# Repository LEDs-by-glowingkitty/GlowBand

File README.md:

GlowBand is an exciting LED wristband. For dancing at parties and festivals, for long-time exposure photography, and for everyday situations that need some light.

This project started as "The Glowing Arms Project" (check out the "GlowBand v0.1" folder) and after experimenting with making the project smaller and based on existing PCBs ("GlowBand v0.2" folder) I decided to instead make a custom PCB design ("GlowBand v1.0"). The PCB design is still in development, but I plan to finish the design in the coming months. Stay tuned!

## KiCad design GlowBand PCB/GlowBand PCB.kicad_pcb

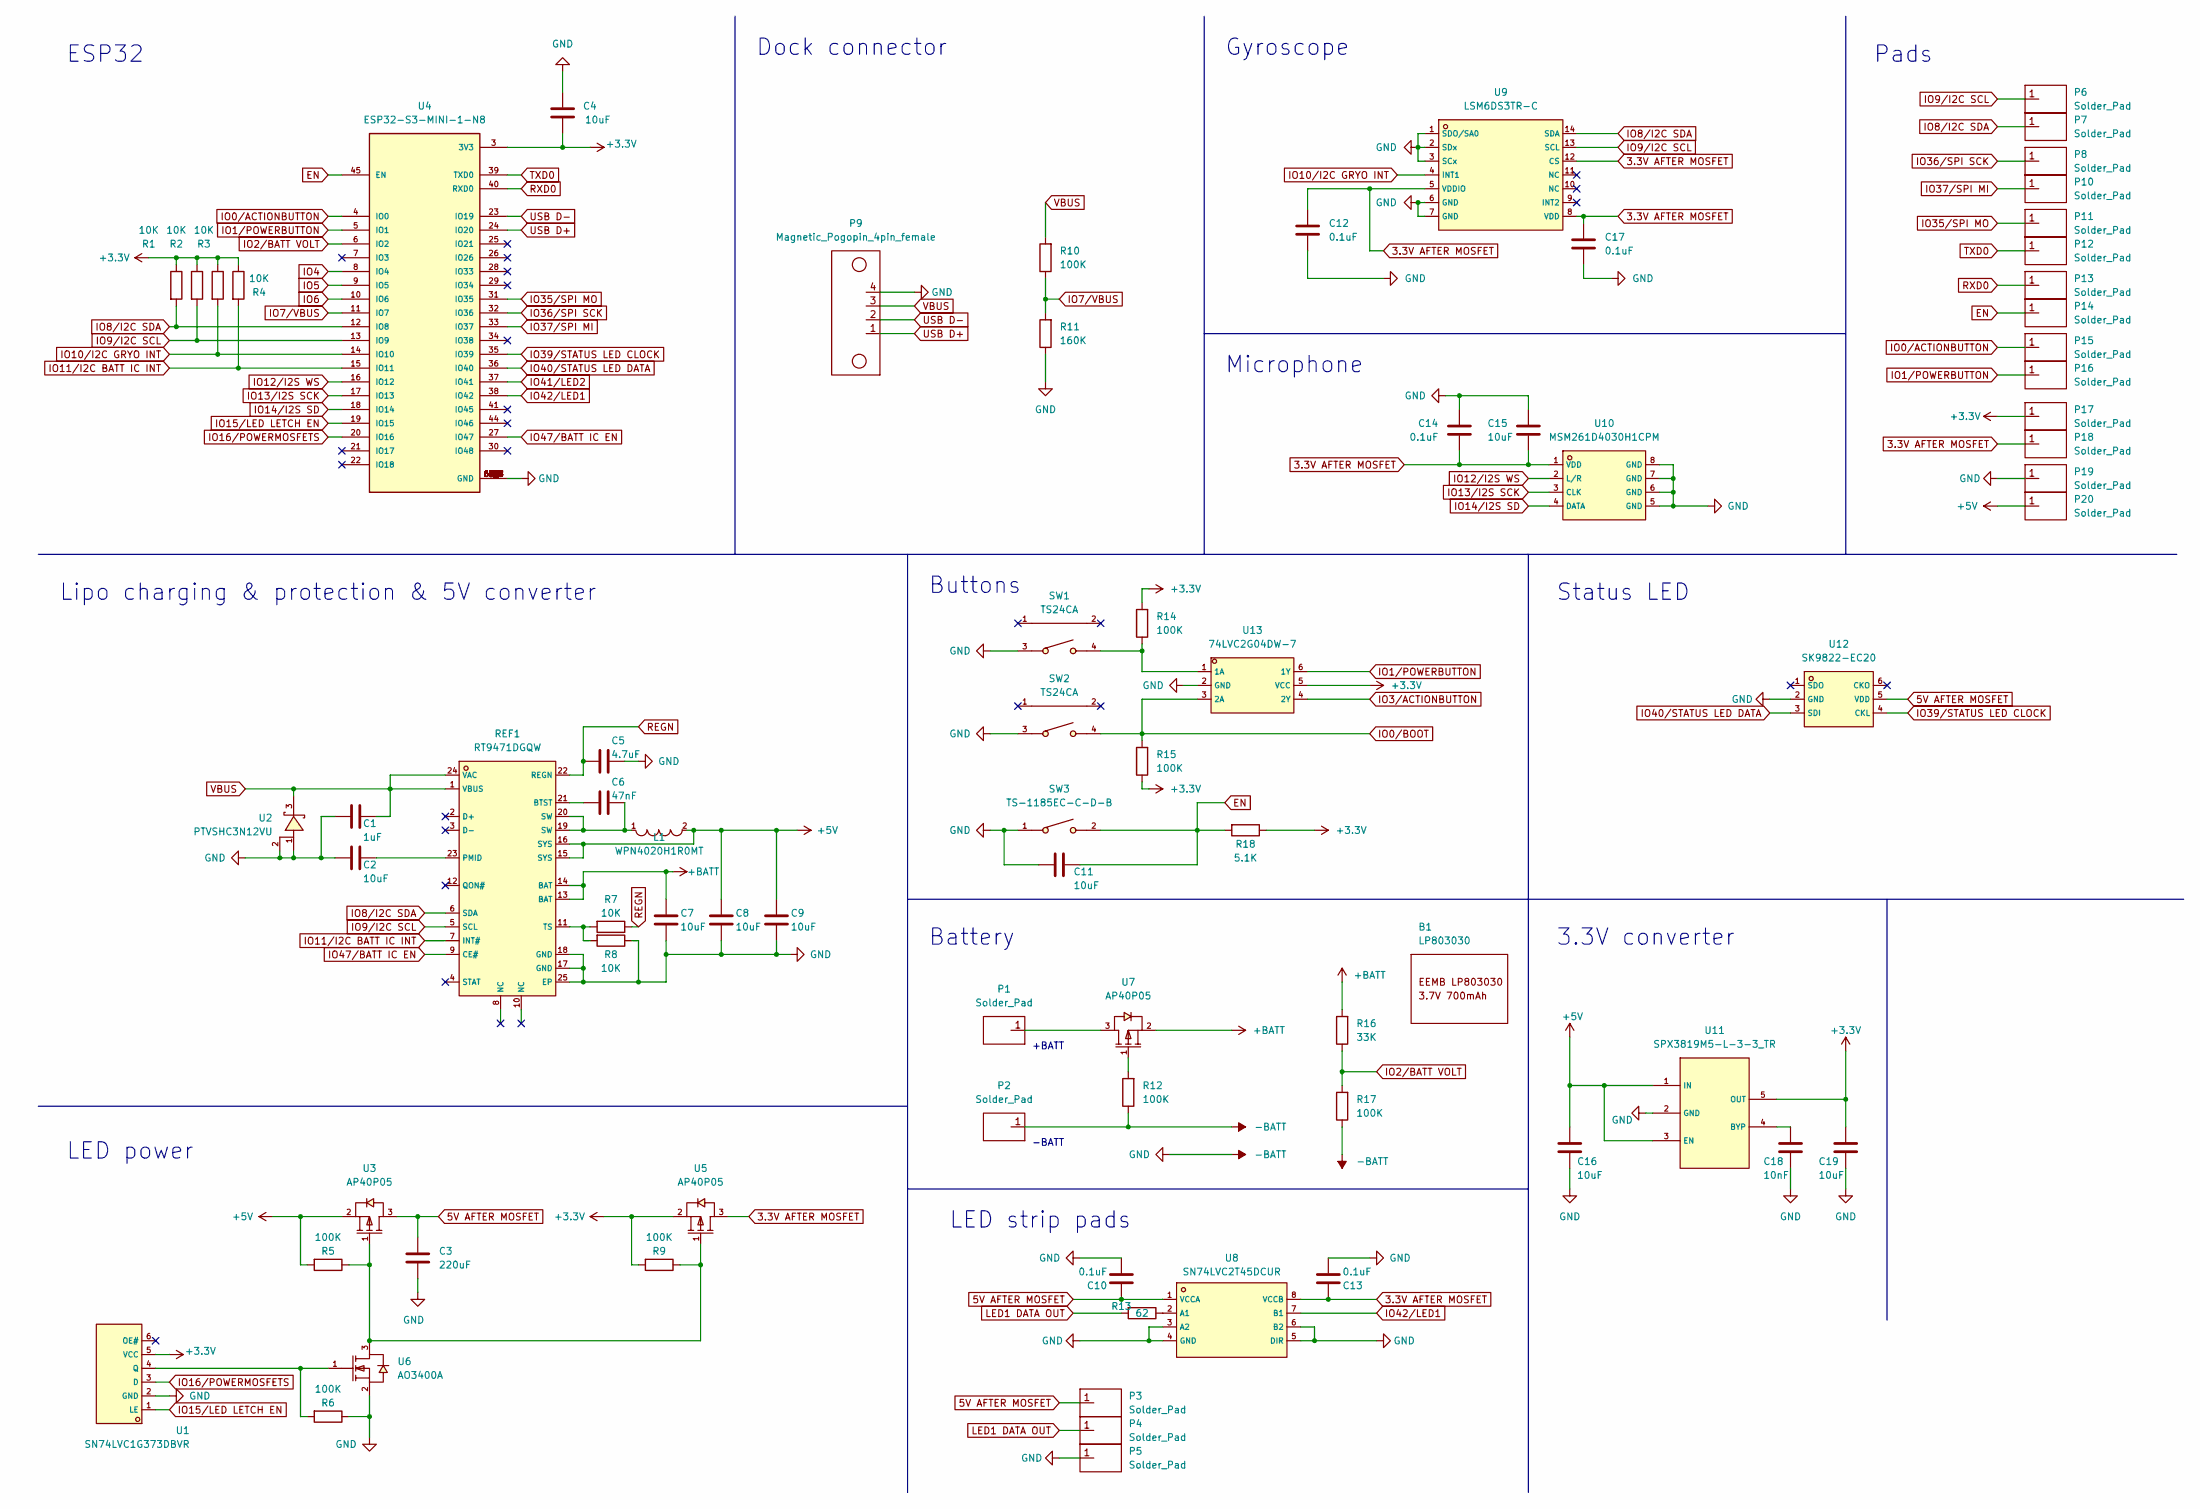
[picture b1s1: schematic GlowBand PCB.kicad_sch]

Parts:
B1: LP803030
C1: 1uF; C_0402_1005Metric; LCSC # C52923
C2, C4, C7, C8, C9, C15, C16, C19: 10uF; C_0603_1608Metric; LCSC # C96446
C3: 220uF; C_1206_3216Metric; LCSC # C412252
C5: 4.7uF; C_0402_1005Metric; LCSC # C23733
C6: 47nF; C_0402_1005Metric; LCSC # C505502
C10, C12, C13, C14, C17: 0.1uF; C_0402_1005Metric; LCSC # C1525
C11: 10uF; C_0603_1608Metric; LCSC # C19702
C18: 10nF; C_0402_1005Metric; LCSC # C15195
L1: WPN4020H1R0MT; IND-SMD_L4.0-W4.0_SLW40XX; LCSC C98359
P1, P2, P3, P4, P5, P6, P7, P8, P10, P11, P12, P13, P14, P15, P16, P17, P18, P19, P20: Solder_Pad; Solder pad
P9: Magnetic_Pogopin_4pin_female; Magnetic Pogopin 4pin female
R1, R2, R3, R4, R7, R8: 10K; R_0402_1005Metric; LCSC # C25744
R5, R6, R9, R10, R12, R14, R15, R17: 100K; R_0402_1005Metric; LCSC # C25741
R11: 160K; R_0603_1608Metric; LCSC # C22813
R13: 62; R_0402_1005Metric; LCSC # C4962
R16: 33K; R_0402_1005Metric; LCSC # C25779
R18: 5.1K; R_0402_1005Metric; LCSC # C25905
REF1: RT9471DGQW; RT9471_vias_in_pad; LCSC C2839437
SW1, SW2: TS24CA; SW-SMD_TS24CA; LCSC C393942
SW3: TS-1185EC-C-D-B; SW-SMD_4P-L3.7-W3.0-P1.50-LS4.7; LCSC # C318893
U1: SN74LVC1G373DBVR; SOT-23-6_L2.9-W1.6-P0.95-LS2.8-BR; LCSC C128413
U2: PTVSHC3N12VU; DFN-3_L2.0-W2.0-P1.30-BR; LCSC C110755
U3, U5, U7: AP40P05; SOT-23-3_L2.9-W1.3-P1.90-LS2.4-BR; LCSC # C2886385
U4: ESP32-S3-MINI-1-N8; LCSC# C2913206
U6: AO3400A; SOT-23-3_L2.9-W1.6-P1.90-LS2.8-BR; LCSC # C20917
U8: SN74LVC2T45DCUR; VSSOP-8_L2.4-W2.1-P0.50-LS3.2-BR; LCSC # C15741
U9: LSM6DS3TR-C; LGA-14_L3.0-W2.5-P0.50-TL; LCSC C967633
U10: MSM261D4030H1CPM; MIC-SMD_8P-L3.0-W4.0-P0.85-BL; LCSC # C966942
U11: SPX3819M5-L-3-3_TR; SOT-23-5_L3.0-W1.7-P0.95-LS2.8-BR; LCSC # C9055
U12: SK9822-EC20; LED-SMD_6P-L2.0-W2.0-P0.80-TL; LCSC C2909059
U13: 74LVC2G04DW-7; SOT-363_L2.0-W1.3-P0.65-LS2.1-BR; LCSC C69053

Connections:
3.3V AFTER MOSFET: C12.1, C13.1, C14.2, C15.2, C17.1, P18.1, U5.3 (D), U8.8 (VCCB), U9.5 (VDDIO), U9.8 (VDD), U9.12 (CS), U10.1 (VDD)
5V AFTER MOSFET: C3.1, C10.1, P3.1, U3.3 (D), U8.1 (VCCA), U12.5 (VDD)
+3V3: C4.2, C19.2, P17.1, R1.1, R2.1, R3.1, R4.1, R9.2, R14.2, R15.1, R18.1, U1.5 (VCC), U4.3 (3V3), U5.2 (S), U11.5 (OUT), U13.5 (VCC)
+5V: C8.2, C9.2, C16.2, L1.2, P20.1, R5.2, REF1.15 (SYS), REF1.16 (SYS), U3.2 (S), U11.1 (IN), U11.3 (EN)
+BATT: C7.2, R16.2, REF1.13 (BAT), REF1.14 (BAT), U7.2 (S)
-BATT: C1.1, C2.1, C3.2, C4.1, C5.2, C7.1, C8.1, C9.1, C10.2, C11.1, C12.2, C13.2, C14.1, C15.1, C16.1, C17.2, C18.1, C19.1, P2.1, P5.1, P9.4, P19.1, R6.1, R8.1, R11.1, R12.1, R17.1, REF1.17 (GND), REF1.18 (GND), REF1.25 (EP), SW1.3, SW2.3, SW3.1, U1.2 (GND), U2.1 (A), U2.2 (1), U4.1 (GND), U4.2 (GND), U4.42 (GND), U4.43 (GND), U4.46 (GND), U4.47 (GND), U4.48 (GND), U4.49 (GND), U4.50 (GND), U4.51 (GND), U4.52 (GND), U4.53 (GND), U4.54 (GND), U4.55 (GND), U4.56 (GND), U4.57 (GND), U4.58 (GND), U4.59 (GND), U4.60 (GND), U4.61 (GND), U4.61_1 (GND), U4.61_2 (GND), U4.61_3 (GND), U4.61_4 (GND), U4.61_5 (GND), U4.61_6 (GND), U4.61_7 (GND), U4.61_8 (GND), U4.62 (GND), U4.63 (GND), U4.64 (GND), U4.65 (GND), U6.2 (S), U8.3 (A2), U8.4 (GND), U8.5 (DIR), U8.6 (B2), U9.1 (SDO/SA0), U9.2 (SDx), U9.3 (SCx), U9.6 (GND), U9.7 (GND), U10.5 (GND), U10.6 (GND), U10.7 (GND), U10.8 (GND), U11.2 (GND), U12.2 (GND), U13.2 (GND)
EN: C11.2, P14.1, R18.2, SW3.2, U4.45 (EN)
IO0/ACTIONBUTTON: P15.1, U4.4 (IO0)
IO0/BOOT: R15.2, SW2.4, U13.3 (2A)
IO1/POWERBUTTON: P16.1, U4.5 (IO1), U13.6 (1Y)
IO2/BATT VOLT: R16.1, R17.2, U4.6 (IO2)
IO3/ACTIONBUTTON: U13.4 (2Y)
IO4: U4.8 (IO4)
IO5: U4.9 (IO5)
IO6: U4.10 (IO6)
IO7/VBUS: R10.1, R11.2, U4.11 (IO7)
IO8/I2C SDA: P7.1, R1.2, REF1.6 (SDA), U4.12 (IO8), U9.14 (SDA)
IO9/I2C SCL: P6.1, R2.2, REF1.5 (SCL), U4.13 (IO9), U9.13 (SCL)
IO10/I2C GRYO INT: R3.2, U4.14 (IO10), U9.4 (INT1)
IO11/I2C BATT IC INT: R4.2, REF1.7 (INT#), U4.15 (IO11)
IO12/I2S WS: U4.16 (IO12), U10.2 (L/R)
IO13/I2S SCK: U4.17 (IO13), U10.3 (CLK)
IO14/I2S SD: U4.18 (IO14), U10.4 (DATA)
IO15/LED LETCH EN: U1.1 (LE), U4.19 (IO15)
IO16/POWERMOSFETS: U1.3 (D), U4.20 (IO16)
IO35/SPI MO: P11.1, U4.31 (IO35)
IO36/SPI SCK: P8.1, U4.32 (IO36)
IO37/SPI MI: P10.1, U4.33 (IO37)
IO39/STATUS LED CLOCK: U4.35 (IO39), U12.4 (CKL)
IO40/STATUS LED DATA: U4.36 (IO40), U12.3 (SDI)
IO41/LED2: U4.37 (IO41)
IO42/LED1: U4.38 (IO42), U8.7 (B1)
IO47/BATT IC EN: REF1.9 (CE#), U4.27 (IO47)
LED1 DATA OUT: P4.1, R13.2
unnamed: C2.2, REF1.23 (PMID)
unnamed: C6.1, REF1.21 (BTST)
unnamed: C6.2, L1.1, REF1.19 (SW), REF1.20 (SW)
unnamed: C18.2, U11.4 (BYP)
unnamed: P1.1, U7.3 (D)
unnamed: R5.1, R9.1, U3.1 (G), U5.1 (G), U6.3 (D)
unnamed: R6.2, U1.4 (Q), U6.1 (G)
unnamed: R7.2, R8.2, REF1.11 (TS)
unnamed: R12.2, U7.1 (G)
unnamed: R13.1, U8.2 (A1)
unnamed: R14.1, SW1.4, U13.1 (1A)
REGN: C5.1, R7.1, REF1.22 (REGN)
RXD0: P13.1, U4.40 (RXD0)
TXD0: P12.1, U4.39 (TXD0)
USB D+: P9.1, U4.24 (IO20)
USB D-: P9.2, U4.23 (IO19)
VBUS: C1.2, P9.3, R10.2, REF1.1 (VBUS), REF1.24 (VAC), U2.3 (K)

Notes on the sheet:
+BATT
Dock connector
ESP32
LED strip pads
Buttons
LED power
3.3V converter
Status LED
Gyroscope
Microphone
-BATT
Lipo charging & protection & 5V converter
Pads
Battery

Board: 2 copper layers, 76 parts (18 on the bottom side), 46 nets, no tracks yet.

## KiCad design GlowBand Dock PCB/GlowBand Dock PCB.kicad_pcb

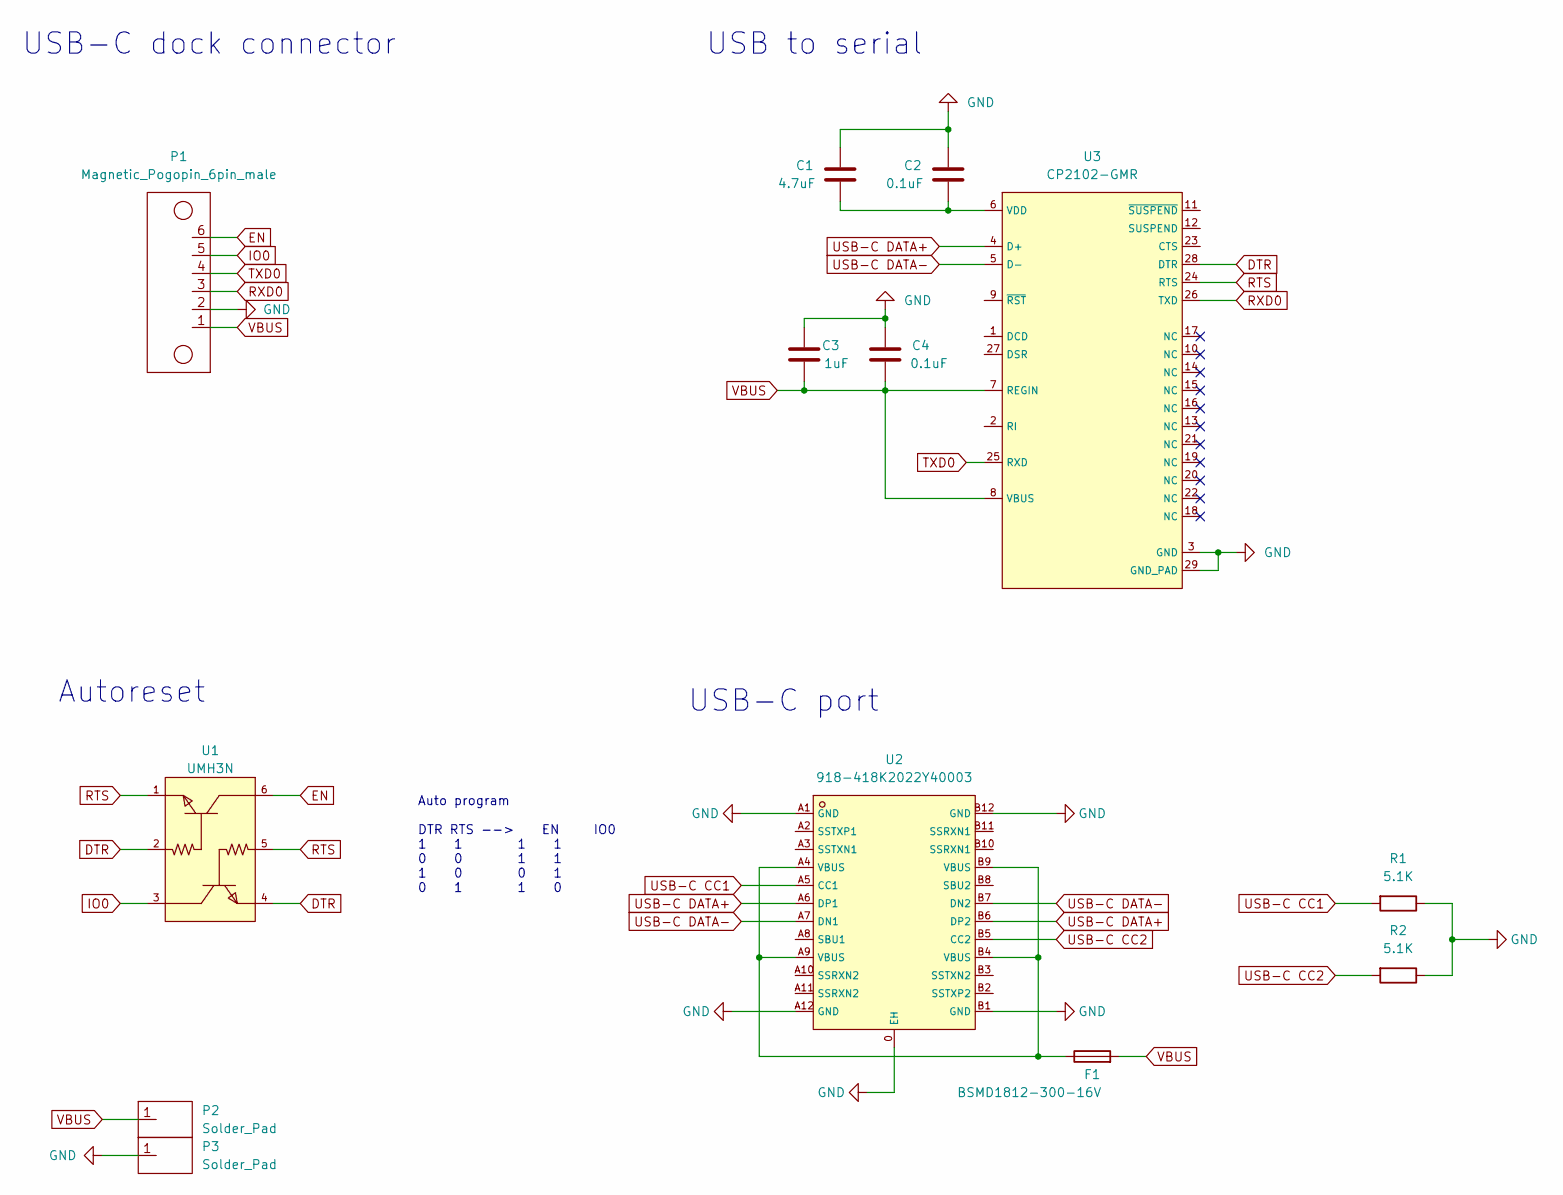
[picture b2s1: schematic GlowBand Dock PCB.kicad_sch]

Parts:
C1: 4.7uF; C_0603_1608Metric; LCSC # C19666
C2, C4: 0.1uF; C_0402_1005Metric; LCSC # C1525
C3: 1uF; C_0402_1005Metric; LCSC # C52923
F1: BSMD1812-300-16V; Fuse_1812_4532Metric; LCSC # C883162
P1: Magnetic_Pogopin_6pin_male; Magnetic Pogopin 6pin male
P2, P3: Solder_Pad; Solder pad
R1, R2: 5.1K; R_0402_1005Metric; LCSC # C25905
U1: UMH3N; SC-70-6_L2.2-W1.3-P0.65-LS2.1-BR; LCSC # C62892
U2: 918-418K2022Y40003; TYPE-C-SMD_918-418K2022Y40003; LCSC C67382
U3: CP2102-GMR; QFN-28_L5.0-W5.0-P0.50-BL-EP; LCSC # C6568

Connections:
DTR: U1.2 (B), U1.4 (E), U3.28 (DTR)
EN: P1.6, U1.6 (C)
GND: C1.2, C2.1, C3.2, C4.2, P1.2, P3.1, R1.1, R2.1, U2.0 (EH), U2.A1 (GND), U2.A12 (GND), U2.B1 (GND), U2.B12 (GND), U3.3 (GND), U3.29 (GND_PAD)
IO0: P1.5, U1.3 (C)
unnamed: C1.1, C2.2, U3.6 (VDD)
unnamed: F1.1, U2.A4 (VBUS), U2.A9 (VBUS), U2.B4 (VBUS), U2.B9 (VBUS)
RTS: U1.1 (E), U1.5 (B), U3.24 (RTS)
RXD0: P1.3, U3.26 (TXD)
TXD0: P1.4, U3.25 (RXD)
USB-C CC1: R1.2, U2.A5 (CC1)
USB-C CC2: R2.2, U2.B5 (CC2)
USB-C DATA+: U2.A6 (DP1), U2.B6 (DP2), U3.4 (D+)
USB-C DATA-: U2.A7 (DN1), U2.B7 (DN2), U3.5 (D-)
VBUS: C3.1, C4.1, F1.2, P1.1, P2.1, U3.7 (REGIN), U3.8 (VBUS)

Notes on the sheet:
Autoreset
USB-C port
USB-C dock connector
USB to serial
Auto program DTR RTS --> EN IO0 1 1 1 1 0 0 1 1 1 0 0 1 0 1 1 0

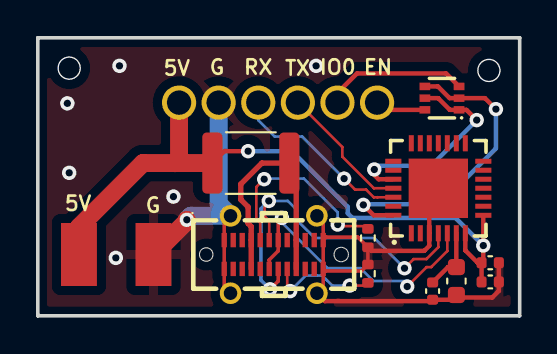
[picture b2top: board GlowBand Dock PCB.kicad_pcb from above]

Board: 2 copper layers, 26.8 x 15.4 mm, 13 parts (1 on the bottom side), 14 nets.

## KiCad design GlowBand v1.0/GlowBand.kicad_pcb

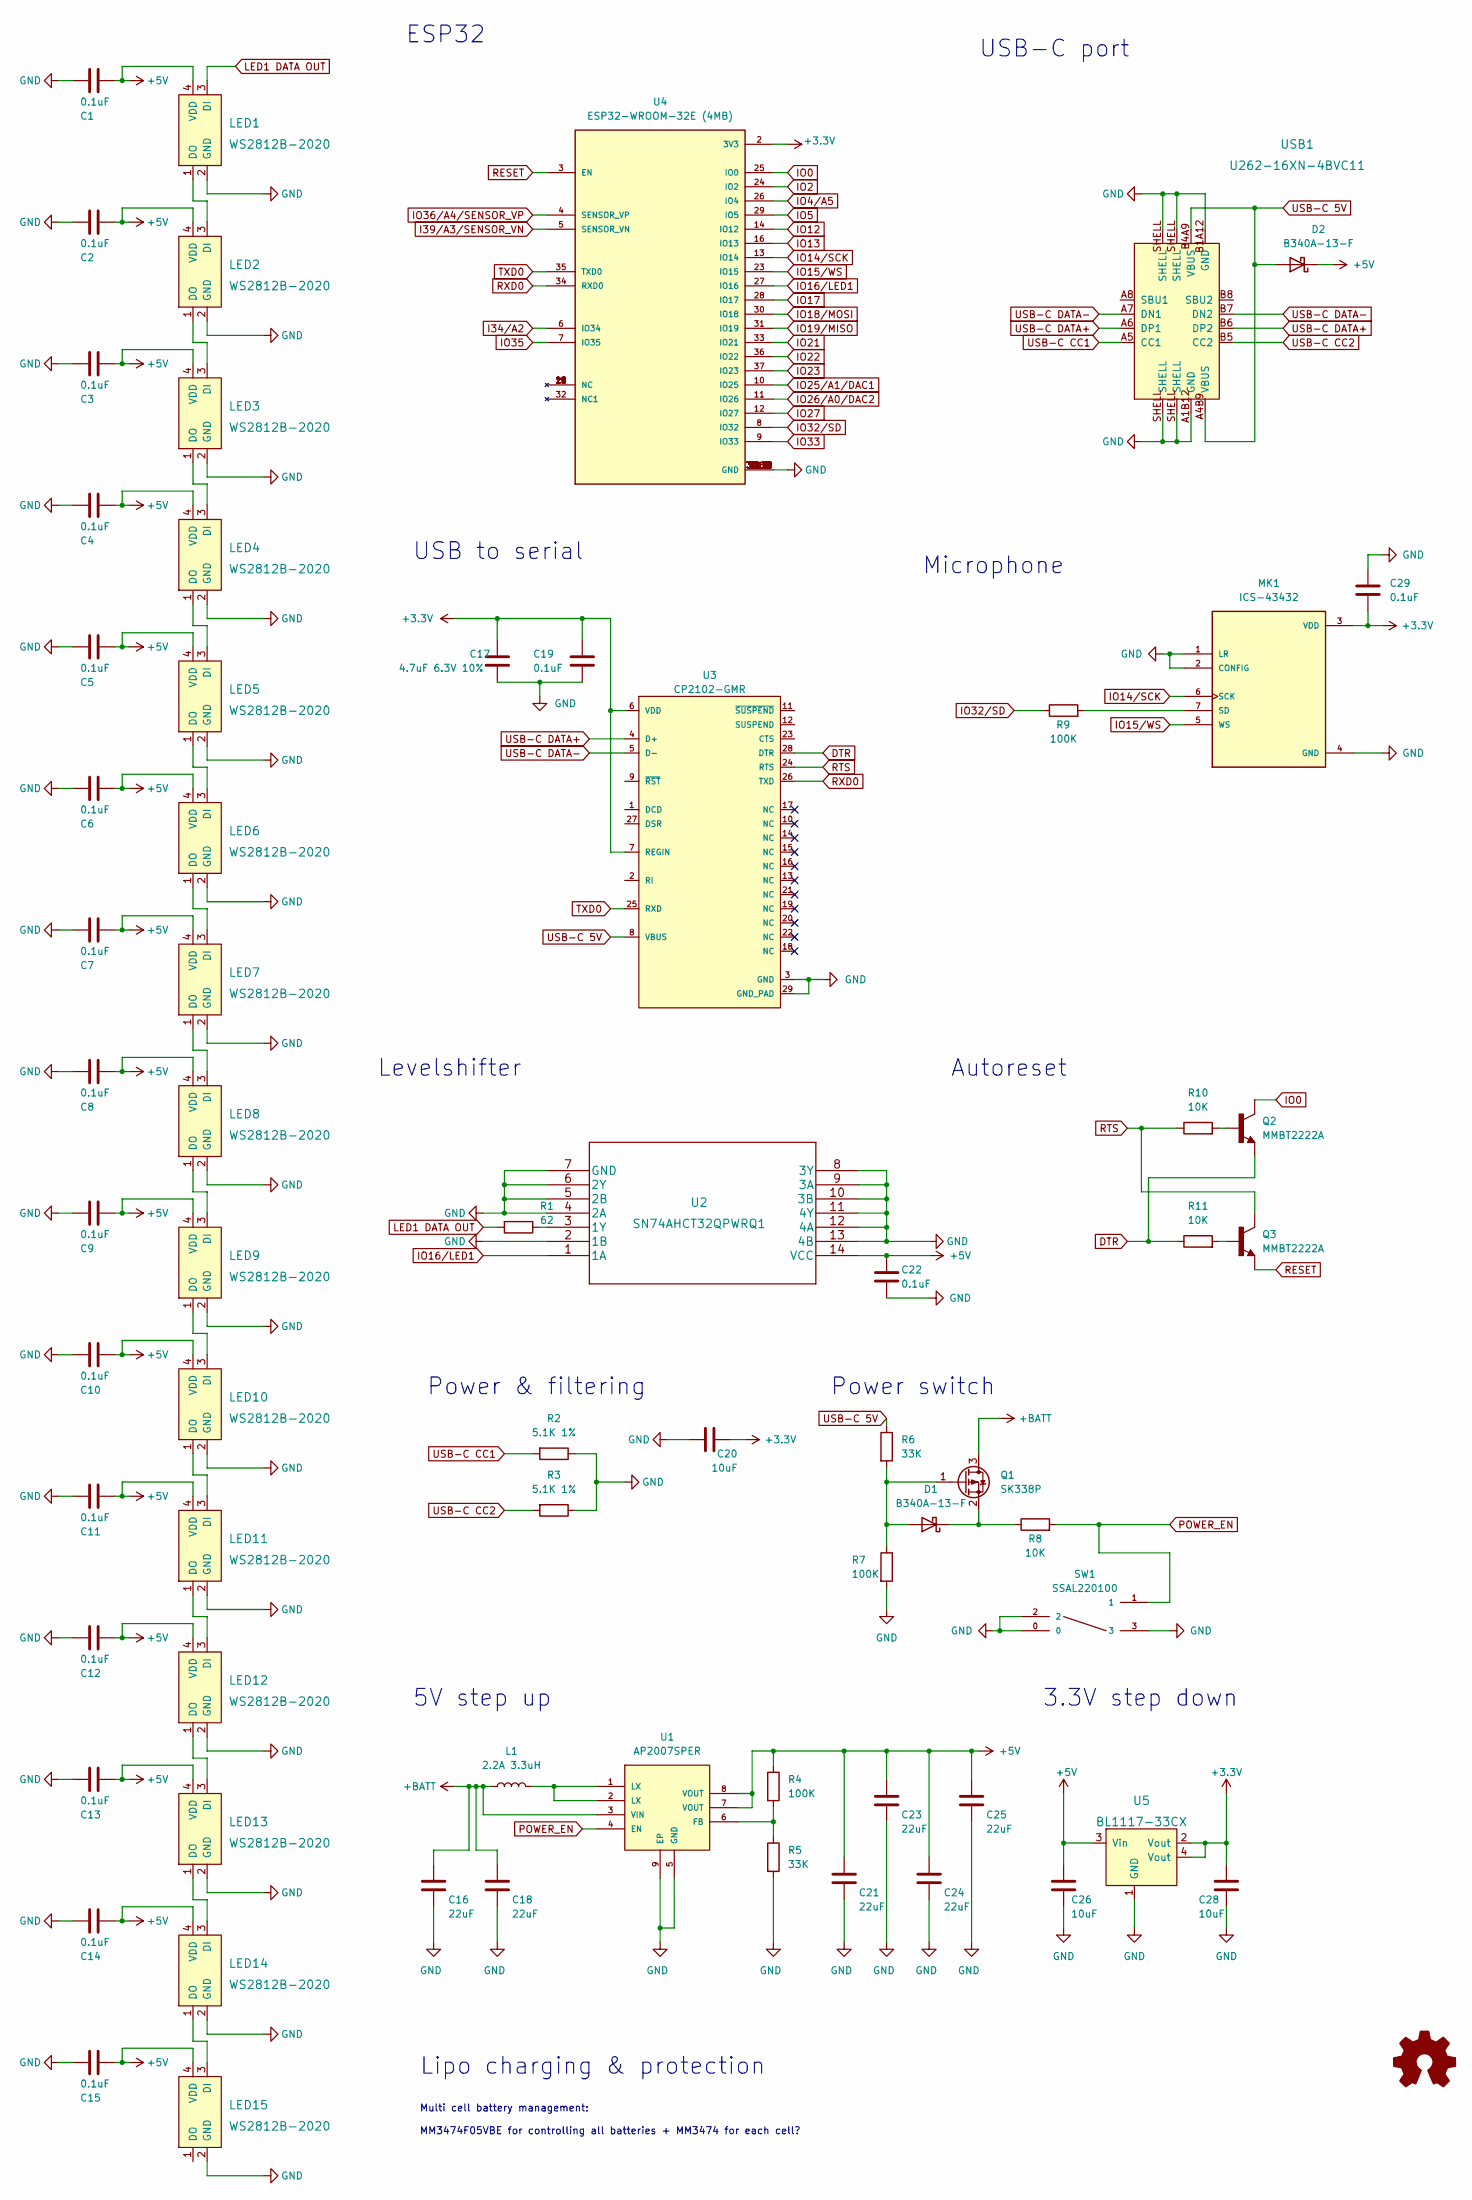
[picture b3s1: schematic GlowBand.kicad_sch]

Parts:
C1, C2, C3, C4, C5, C6, C7, C8, C9, C10, C11, C12, C13, C14, C15: 0.1uF; C_0603_1608Metric; Mfr. Part # 06035C104K4Z2A; LCSC Part # C597194
C16, C18, C21, C23, C24, C25: 22uF; C_0603_1608Metric_Pad1.08x0.95mm_HandSolder
C17: 4.7uF 6.3V 10%; C_0603_1608Metric_Pad1.08x0.95mm_HandSolder
C19, C29: 0.1uF; C_0603_1608Metric_Pad1.08x0.95mm_HandSolder; Mfr. Part # 06035C104K4Z2A; LCSC Part # C597194
C20, C26, C28: 10uF; C_0603_1608Metric_Pad1.08x0.95mm_HandSolder; Mfr. Part # C0603X5R106K250NT; LCSC Part # C729457
C22: 0.1uF; C_0603_1608Metric_Pad1.08x0.95mm_HandSolder
D1, D2: B340A-13-F; D_SMA; Mfr. Part # B340A-13-F; LCSC Part # C85098
L1: 2.2A 3.3uH; FDSD0412
LED1, LED2, LED3, LED4, LED5, LED6, LED7, LED8, LED9, LED10, LED11, LED12, LED13, LED14, LED15: WS2812B-2020; Mfr. Part # WS2812B-2020; LCSC Part # C965555
MK1: ICS-43432; MIC_ICS-43432; Mfr. Part # ICS-43432; LCSC Part # C574021
Q1: SK338P; SOT-23; Mfr. Part # SK338P; LCSC Part # C475695
Q2, Q3: MMBT2222A; SOT-23; Mfr. Part # MMBT2222A; LCSC Part # C545537
R1: 62; R_0603_1608Metric_Pad0.98x0.95mm_HandSolder
R2, R3: 5.1K 1%; R_0603_1608Metric_Pad0.98x0.95mm_HandSolder; Mfr. Part # HPCR0603F5K10K9; LCSC Part # C365193
R4, R7, R9: 100K; R_0603_1608Metric_Pad0.98x0.95mm_HandSolder; Mfr. Part # 0603WAF1003T5E; LCSC Part # C25803
R5, R6: 33K; R_0603_1608Metric_Pad0.98x0.95mm_HandSolder
R8: 10K; R_0603_1608Metric_Pad0.98x0.95mm_HandSolder
R10, R11: 10K; R_0603_1608Metric_Pad0.98x0.95mm_HandSolder; Mfr. Part # RC0603FR-0710KL; LCSC Part # C98220
SW1: SSAL220100
U1: AP2007SPER; Mfr. Part # AP2007SPER; LCSC Part # C130338
U2: SN74AHCT32QPWRQ1; Mfr. Part # SN74AHCT32QPWRQ1; LCSC Part # C507218
U3: CP2102-GMR; mouser part number 634-CP2102-GMR; digikey description USB Bridge, USB to UART USB 2.0 UART In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
U4: ESP32-WROOM-32E (4MB); MODULE_ESP32-WROOM-32E_(16MB); Mfr. Part # ESP32-WROOM-32E(4MB); LCSC Part # C701341
U5: BL1117-33CX; SOT-223; Mfr. Part # BL1117-33CX; LCSC Part # C5400
USB1: U262-16XN-4BVC11; USB-3.1-SMD_U262-161N-4BVC11; Mfr. Part # U262-161N-4BVC11; LCSC Part # C319148

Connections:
+3V3: C17.2, C19.1, C20.1, C28.2, C29.2, MK1.3 (VDD), U3.6 (VDD), U3.7 (REGIN), U4.2 (3V3), U5.2 (Vout), U5.4 (Vout)
+5V: C1.1, C2.1, C3.1, C4.1, C5.1, C6.1, C7.1, C8.1, C9.1, C10.1, C11.1, C12.1, C13.1, C14.1, C15.1, C21.1, C22.1, C23.1, C24.1, C25.1, C26.2, D2.1 (K), LED1.4 (VDD), LED2.4 (VDD), LED3.4 (VDD), LED4.4 (VDD), LED5.4 (VDD), LED6.4 (VDD), LED7.4 (VDD), LED8.4 (VDD), LED9.4 (VDD), LED10.4 (VDD), LED11.4 (VDD), LED12.4 (VDD), LED13.4 (VDD), LED14.4 (VDD), LED15.4 (VDD), R4.1, U1.7 (VOUT), U1.8 (VOUT), U2.14 (VCC), U5.3 (Vin)
+BATT: C16.1, C18.1, L1.1, Q1.3 (D), U1.3 (VIN)
DTR: Q2.2, R11.1, U3.28 (DTR)
GND: C1.2, C2.2, C3.2, C4.2, C5.2, C6.2, C7.2, C8.2, C9.2, C10.2, C11.2, C12.2, C13.2, C14.2, C15.2, C16.2, C17.1, C18.2, C19.2, C20.2, C21.2, C22.2, C23.2, C24.2, C25.2, C26.1, C28.1, C29.1, LED1.2 (GND), LED2.2 (GND), LED3.2 (GND), LED4.2 (GND), LED5.2 (GND), LED6.2 (GND), LED7.2 (GND), LED8.2 (GND), LED9.2 (GND), LED10.2 (GND), LED11.2 (GND), LED12.2 (GND), LED13.2 (GND), LED14.2 (GND), LED15.2 (GND), MK1.1 (LR), MK1.2 (CONFIG), MK1.4 (GND), R2.1, R3.1, R5.2, R7.2, SW1.0, SW1.2, SW1.3, U1.5 (GND), U1.9 (EP), U2.2 (1B), U2.4 (2A), U2.5 (2B), U2.6 (2Y), U2.7 (GND), U2.8 (3Y), U2.9 (3A), U2.10 (3B), U2.11 (4Y), U2.12 (4A), U2.13 (4B), U3.3 (GND), U3.29 (GND_PAD), U4.1 (GND), U4.15 (GND), U4.38 (GND), U4.39_1 (GND), U4.39_2 (GND), U4.39_3 (GND), U4.39_4 (GND), U4.39_5 (GND), U4.39_6 (GND), U4.39_7 (GND), U4.39_8 (GND), U4.39_9 (GND), U4.39_10 (GND), U4.39_11 (GND), U4.39_12 (GND), U4.39_13 (GND), U4.39_14 (GND), U4.39_15 (GND), U4.39_16 (GND), U4.39_17 (GND), U4.39_18 (GND), U4.39_19 (GND), U4.39_20 (GND), U4.39_21 (GND), U5.1 (GND), USB1.A1B12 (GND), USB1.B1A12 (GND), USB1.SHELL
I34/A2: U4.6 (IO34)
I39/A3/SENSOR_VN: U4.5 (SENSOR_VN)
IO0: Q2.3, U4.25 (IO0)
IO2: U4.24 (IO2)
IO4/A5: U4.26 (IO4)
IO5: U4.29 (IO5)
IO12: U4.14 (IO12)
IO13: U4.16 (IO13)
IO14/SCK: MK1.6 (SCK), U4.13 (IO14)
IO15/WS: MK1.5 (WS), U4.23 (IO15)
IO16/LED1: U2.1 (1A), U4.27 (IO16)
IO17: U4.28 (IO17)
IO18/MOSI: U4.30 (IO18)
IO19/MISO: U4.31 (IO19)
IO21: U4.33 (IO21)
IO22: U4.36 (IO22)
IO23: U4.37 (IO23)
IO25/A1/DAC1: U4.10 (IO25)
IO26/A0/DAC2: U4.11 (IO26)
IO27: U4.12 (IO27)
IO32/SD: R9.1, U4.8 (IO32)
IO33: U4.9 (IO33)
IO35: U4.7 (IO35)
IO36/A4/SENSOR_VP: U4.4 (SENSOR_VP)
LED1 DATA OUT: LED1.3 (DI), R1.2
unnamed: D1.1 (K), Q1.2 (S), R8.1
unnamed: D1.2 (A), Q1.1 (G), R6.2, R7.1
unnamed: L1.2, U1.1 (LX), U1.2 (LX)
unnamed: LED1.1 (DO), LED2.3 (DI)
unnamed: LED2.1 (DO), LED3.3 (DI)
unnamed: LED4.1 (DO), LED5.3 (DI)
unnamed: LED3.1 (DO), LED4.3 (DI)
unnamed: LED6.1 (DO), LED7.3 (DI)
unnamed: LED5.1 (DO), LED6.3 (DI)
unnamed: LED7.1 (DO), LED8.3 (DI)
unnamed: LED8.1 (DO), LED9.3 (DI)
unnamed: LED10.1 (DO), LED11.3 (DI)
unnamed: LED9.1 (DO), LED10.3 (DI)
unnamed: LED11.1 (DO), LED12.3 (DI)
unnamed: LED13.1 (DO), LED14.3 (DI)
unnamed: LED12.1 (DO), LED13.3 (DI)
unnamed: LED14.1 (DO), LED15.3 (DI)
unnamed: MK1.7 (SD), R9.2
unnamed: Q2.1, R10.2
unnamed: Q3.1, R11.2
unnamed: R1.1, U2.3 (1Y)
unnamed: R4.2, R5.1, U1.6 (FB)
POWER_EN: R8.2, SW1.1, U1.4 (EN)
RESET: Q3.2, U4.3 (EN)
RTS: Q3.3, R10.1, U3.24 (RTS)
RXD0: U3.26 (TXD), U4.34 (RXD0)
TXD0: U3.25 (RXD), U4.35 (TXD0)
USB-C 5V: D2.2 (A), R6.1, U3.8 (VBUS), USB1.A4B9 (VBUS), USB1.B4A9 (VBUS)
USB-C CC1: R2.2, USB1.A5 (CC1)
USB-C CC2: R3.2, USB1.B5 (CC2)
USB-C DATA+: U3.4 (D+), USB1.A6 (DP1), USB1.B6 (DP2)
USB-C DATA-: U3.5 (D-), USB1.A7 (DN1), USB1.B7 (DN2)

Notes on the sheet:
ESP32
3.3V step down
USB to serial
Power switch
USB-C port
5V step up
Lipo charging & protection
Microphone
Power & filtering
Multi cell battery management: MM3474F05VBE for controlling all batteries + MM3474 for each cell?
Autoreset
Levelshifter

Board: 2 copper layers, 68 parts (1 on the bottom side), 43 nets, no tracks yet.

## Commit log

2020-05-18 add instruction
2020-05-25 update donate button
2020-05-29 add patreon link
2020-05-30 update link
2020-08-18 replaced outdated "How to build" instruction with new link to video
2022-02-01 added pcb design for new v1.0 (in dev)
2022-02-01 updated readmes
2022-08-24 started new design
2022-11-11 start creating new pcbs
2022-11-16 updated pcbs
2022-11-23 added gyroscope to GlowBand
2022-12-03 added pinout
2022-12-04 update pinout naming
2022-12-04 added pinout legend
2022-12-05 updated pinout
2022-12-06 added pdf qr code to pinout
2023-02-05 updated pcb design and case prototype

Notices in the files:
parts and their libraries:
Copyright 2021 Accelerated Designs. All rights reserved.
